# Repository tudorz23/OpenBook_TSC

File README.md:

*Designed by Marius-Tudor Zaharia, 333CA, March 2025*

# OpenBook

---

## What is OpenBook?
* OpenBook is an implementation of a performant, yet accessible e-book reader,
following an open-source philosophy, with Wi-Fi connectivity.
* It focuses on minimalism and offers a distraction-free body, with three
physical buttons for efficient navigation.
* It also promotes environmental awareness, encompassing temperature, humidity,
air pressure and air quality sensors.

---

## Block diagram

---

## Hardware description
### PCB
* The design of the PCB is centered around an **ESP32 C6 WROOM** microcontroller,
equipped with a 32-bit RISC-V single-core processor, up to 160MHz.
    * It offers 320 KB ROM, 512KB HP SRAM, 16KB LP SRAM.
    * It comes with Wi-Fi 6 and Bluetooth LE connectivity.
    * Supports GPIO, SPI, UART, I2C, LED PWM.

* The **ESP32** supports *5 power modes*, each with a different power consumption index:
    * *Active* - between 160 and 260mA
    * *Modem Sleep* - between 3 and 20mA
    * *Light Sleep* - 0.8mA
    * *Deep Sleep* - 10uA
    * *Hibernation* - 2.5uA

* **Three Buttons** are connected to 3 GPIO pins of the ESP32, allowing the user
                    to control the device:
    * *Reset* to **pin 3 - Enable**
    * *Boot* to **pin 15 - GPIO 9**
    * *Change* to **pin 23 - GPIO 15**

* **SD Card** socket, which communicates by SPI protocol:
    * *pin 2 - CD/DAT3* to **pin 4 - GPIO 4**
    * *pin 3 - CMD* to **pin 7** (MOSI, i.e. Serial Data Out, for SPI)
    * *pin 7 - DAT0* to **pin 27** (MISO, i.e. Serial Data In, for SPI)
    * *pin 5* to **pin 6 - clock**

* **E-Paper Display Header**, interfacing the external E-Ink Display, also by SPI.

* **External NOR Flash Memory 64MB**, by SPI too:
    * *pin 1 - CS* to **pin 12 - GPIO 11**
    * *pin 2* to **MOSI** (for SPI)
    * *pin 5* to **MISO** (for SPI)
    * *pin 6* to **pin 6 - clock**

* **RTC Module** - Real Time Clock, using I2C protocol:
    * *pin 4 - Reset* to **pin 16 - GPIO 18**
    * *pin 16 - SCL* to **pin 20 - GPIO 22** (for I2C)
    * *pin 15 - SDA* to **pin 19 - GPIO 21** (for I2C)
    * *pin 1* to **pin 9 - GPIO 1** (for 32KHz)
    * *pin 3 - SQW/INT* to **pin 8 - GPIO 0**
    * Has a battery backup input for continuous timekeeping.

* **BME688** - Digital low power pressure, temperature, humidity and gas sensor,
               also interfaced through I2C:
    * *pin 4 - SCK* to **pin 20 - GPIO 22** (SCL for I2C)
    * *pin 15 - SDI* to **pin 19 - GPIO 21** (SDA for I2C)
    * *pins 2, 6, 8* to **pin 17 - GPIO 19** (for I2C PW)
    * Power consumption is 3.7uA at 1Hz humidity, pressure and temperature scan
        and 0.15uA in sleep mode.

* **USB-C connector** - for fast, efficient charging.

* **Li-Po Battery Charging Controller** - MCP73831

* **LDO Voltage Regulator**

* **Battery Charge Level** - *MAX17048G+T10*, communicates by I2C interface:
    * *pin 7 - SCL* to **pin 20 - GPIO 22**
    * *pin 8 - SDA* to **pin 19 - GPIO 21**
    * Power consumption is 23uA in Active state and 3uA in Hibernate.

### External
* **7.5" E-Paper Display**
* **2500mAh Battery - LP584174**

---

## Bill Of Materials
| Component | Price (EUR) | Count | Provider | Datasheet |
| :---      | :---        | :---  | :---     | :---      |
| ESP32 C6| 2.99 | 1 | https://eu.mouser.com/ProductDetail/Espressif-Systems/ESP32-C6-WROOM-1U-N8?qs=1Kr7Jg1SGW%2FzPU4G%252ByMwkA%3D%3D | https://eu.mouser.com/datasheet/2/891/Espressif_Systems_7_11_2023_esp32_c6_wroom_1_wroom-3236277.pdf |
| USB-C connector| 0.39 | 1 | https://eu.mouser.com/ProductDetail/Same-Sky/UJC-H-G-SMT-2-P6-TR?qs=IKkN%2F947nfApFV8T6rOqww%3D%3D |https://eu.mouser.com/datasheet/2/1628/ujc_h_g_smt_2_p6_tr-3511211.pdf |
| USBLC6-2SC6Y | 0.44 | 1 | https://eu.mouser.com/ProductDetail/STMicroelectronics/USBLC6-2SC6Y?qs=gNDSiZmRJS%2FOgDexvXkdow%3D%3D | https://eu.mouser.com/datasheet/2/389/usblc6_2sc6y-1852505.pdf |
| PFMF.050.1 | 0.28 | 1 | https://eu.mouser.com/ProductDetail/Schurter/PFMF.050.2?qs=1auRipcfynCums5v1iucSA%3D%3D | https://eu.mouser.com/datasheet/2/358/typ_PFMF-1275918.pdf |
| DMG2305UX-7 | 0.19 | 2 | https://eu.mouser.com/ProductDetail/Diodes-Incorporated/DMG2305UX-7?qs=L1DZKBg7t5F%2FNBHrjfxC%252Bg%3D%3D | https://www.diodes.com/assets/Datasheets/DMG2305UX.pdf |
| SD0805S020S1R0 | 0.3 | 2 | https://eu.mouser.com/ProductDetail/KYOCERA-AVX/SD0805S020S1R0?qs=jCA%252BPfw4LHbpkAoSnwrdjw%3D%3D | https://eu.mouser.com/datasheet/2/40/schottky-3165252.pdf |
| XC6220A331MR-G | 1.46 | 1 | https://eu.mouser.com/ProductDetail/Torex-Semiconductor/XC6220A331MR-G?qs=AsjdqWjXhJ8ZSWznL1J0gg%3D%3D | https://eu.mouser.com/datasheet/2/760/xc6220-3371556.pdf |
| TANT Capacitor | 0.68 | 1 | https://eu.mouser.com/ProductDetail/Vishay-Sprague/293D107X9010D2TE3?qs=8dfOI6wKXonVqFgS8%252BQ%2FMA%3D%3D | https://www.vishay.com/docs/40002/293d.pdf |
| 112A-TAAR-R03 | 1.1 | 1 | https://store.comet.srl.ro/Catalogue/Product/43497/ | https://store.comet.bg/download-file.php?id=27596 |
| 68uH inductance | 0.9 | 1 | https://eu.mouser.com/ProductDetail/Vishay-Dale/IFDC5050JZER680M?qs=iLKYxzqNS745SePZd8tBoA%3D%3D | https://www.vishay.com/docs/34635/ifdc5050jz.pdf |
| MBR0530 | 0.14 | 3 | https://eu.mouser.com/ProductDetail/Micro-Commercial-Components-MCC/MBR0530-TP?qs=KFo7JewZbUECRHkxGanrdg%3D%3D | https://eu.mouser.com/datasheet/2/258/MBR0520_MBR0580_SOD123_-2492194.pdf |
| SI1308EDL-T1-GE3 | 0.42 | 2 | https://eu.mouser.com/ProductDetail/Vishay-Semiconductors/SI1308EDL-T1-GE3?qs=bX1%252BNvsK%2FBramh9tgpOaEw%3D%3D | https://www.vishay.com/docs/63399/si1308edl.pdf |
| Capacitor 0.1uF | 0.3 | 1 | https://eu.mouser.com/ProductDetail/KYOCERA-AVX/KGF21BR71H104KT?qs=Jm2GQyTW%2FbjYyKCvVWAEOw%3D%3D | https://eu.mouser.com/datasheet/2/40/KGF-3223650.pdf |
| Capacitor 1uF | 0.13 | 10 | https://eu.mouser.com/ProductDetail/TAIYO-YUDEN/MAASL105CC7105MFCA01?qs=HFfMDpzxxd1Fn%2FInbJA7vw%3D%3D | https://eu.mouser.com/datasheet/2/396/TAIYO_YUDEN_04_27_2024_c_mlcc_A_e1-3451516.pdf |
| Capacitor 4.7uF | 0.23 | 5 | https://eu.mouser.com/ProductDetail/KYOCERA-AVX/CM05X5R475M16AH?qs=doiCPypUmgFT1xquZKhWtQ%3D%3D | https://eu.mouser.com/datasheet/2/40/Kyocera_AVX_Components_CM025_CM05_CM105_CM21_E217K-2932876.pdf |
| Capacitor 10 uF | 0.47 | 1 | https://eu.mouser.com/ProductDetail/TDK/CGA3EDX7T1A106M080AU?qs=ZcfC38r4PovL%2FBNBUzzBFw%3D%3D | https://product.tdk.com/system/files/dam/doc/product/capacitor/ceramic/mlcc/catalog/mlcc_automotive_general_en.pdf |
| Capacitor 100nF | 0.3 | 8 | https://eu.mouser.com/ProductDetail/KYOCERA-AVX/KAM21BR71H104JT?qs=Jm2GQyTW%2Fbic6Zk4McEt6w%3D%3D | https://eu.mouser.com/datasheet/2/40/AutoMLCCKAM-3216307.pdf |
| Resistor 0.47 | 0.3 | 1 | https://eu.mouser.com/ProductDetail/SEI-Stackpole/RNCL1210FT50L0?qs=17ckDYBRdelVLOJ%252BDFjlUw%3D%3D | https://eu.mouser.com/datasheet/2/385/sei_rncl-3223524.pdf |
| Resistor 2.2 | 0.13 | 1 | https://eu.mouser.com/ProductDetail/YAGEO/RT1206FRE072R2L?qs=XhSZopxZ3H6S0nYZD83pAA%3D%3D | https://eu.mouser.com/datasheet/2/447/PYu_RT_1_to_0_01_RoHS_L_15-3461507.pdf |
| Resistor 15 | 0.25 | 1 | https://eu.mouser.com/ProductDetail/Panasonic/ERA-6AHD150V?qs=MNPzkKEzRtQip8ZeekU%252BRw%3D%3D | https://industrial.panasonic.com/cdbs/www-data/pdf/RDM0000/AOA0000C307.pdf |
Resistor 200 | 0.33 | 1 | https://eu.mouser.com/ProductDetail/TE-Connectivity-Holsworthy/RP73C2B200RFTDF?qs=n4i9pByFsMR0dWGpf721CA%3D%3D | https://eu.mouser.com/datasheet/2/418/10/ENG_DS_1773272_M1-1588495.pdf |
| Resistor 2k | 0.16 | 1 | https://eu.mouser.com/ProductDetail/Panasonic/ERA-3AED202V?qs=yocZuyCaXdM2cBmjcGkIyA%3D%3D | https://industrial.panasonic.com/cdbs/www-data/pdf/RDM0000/AOA0000C307.pdf |
| Resistor 5k1 | 0.15 | 2 | https://eu.mouser.com/ProductDetail/Vishay-Beyschlag/MCS04020C5101FE000?qs=wTZ%2FFzl837YsKPLPRIXUbg%3D%3D | https://www.vishay.com/docs/28705/mcx0x0xpro.pdf |
| Resistor 10k | 0.32 | 16 | https://eu.mouser.com/ProductDetail/SEI-Stackpole/RNWA0612BTE10K0?qs=IKkN%2F947nfD62pDKWE9ZTQ%3D%3D | https://eu.mouser.com/datasheet/2/385/SEI_RNWA-3473840.pdf |
| Resistor 100K | 0.1 | 1 | https://eu.mouser.com/ProductDetail/Panasonic/ERA-3AED104V?qs=MNPzkKEzRtQIWcmUWL4kjg%3D%3D | https://industrial.panasonic.com/cdbs/www-data/pdf/RDM0000/AOA0000C307.pdf |
| MCP73831 | 0.75 | 1 | https://eu.mouser.com/ProductDetail/Microchip-Technology/MCP73831-2ACI-MC?qs=hH%252BOa0VZEiBneYTVdpuVdg%3D%3D | https://eu.mouser.com/datasheet/2/268/MCP73831_Family_Data_Sheet_DS20001984H-3441711.pdf |
| FH34SRJ-24S-0.5SH(99) | 2.6 | 1 | https://eu.mouser.com/ProductDetail/Hirose-Connector/FH34SRJ-24S-0.5SH99?qs=vcbW%252B4%252BSTIpKBl5ap9J8Fw%3D%3D | https://eu.mouser.com/datasheet/2/185/FH34SRJ_24S_0_5SH_99__CL0580_1255_6_99_2DDrawing_0-1615044.pdf |
| BME688 | 9.86 | 1 | https://eu.mouser.com/ProductDetail/Bosch-Sensortec/BME688?qs=IS%252B4QmGtzzqQoVDscqwx3A%3D%3D | https://eu.mouser.com/datasheet/2/783/bst_bme688_fl000-2307034.pdf |
| BD5229G-TR | 0.75 | 1 | https://eu.mouser.com/ProductDetail/ROHM-Semiconductor/BD5229G-TR?qs=4kLU8WoGk0vvnhrrYwdszw%3D%3D | https://fscdn.rohm.com/en/products/databook/datasheet/ic/power/voltage_detector/bd52xxg-e.pdf |
| MAX17048G+T10 | 4.28 | 1 | https://eu.mouser.com/ProductDetail/Analog-Devices-Maxim-Integrated/MAX17048G%2bT10?qs=D7PJwyCwLAoGnnn8jEPRBQ%3D%3D | https://eu.mouser.com/datasheet/2/609/MAX17048_MAX17049-3469099.pdf |
| DS3231SN# | 14.91 | 1 | https://eu.mouser.com/ProductDetail/Analog-Devices-Maxim-Integrated/DS3231SN?qs=1eQvB6Dk1vhUlr8%2FOrV0Fw%3D%3D | https://eu.mouser.com/datasheet/2/609/DS3231-3421123.pdf |
| CPH3225A | 2.33 | 1 | https://eu.mouser.com/ProductDetail/Seiko-Semiconductors/CPH3225A?qs=3etwrb1wR%252BhUOph6lAO7eg%3D%3D | https://eu.mouser.com/datasheet/2/360/Seiko_Instruments_MicroBattery_E_20230330_2024Jan_-3561061.pdf |
| Qwiic | 3.75 | 1 | https://eu.mouser.com/ProductDetail/Adafruit/4208?qs=PzGy0jfpSMtbScLbr0L5dw%3D%3D | https://learn.adafruit.com/introducing-adafruit-stemma-qt/technical-specs |
| PGB1010603MR | 0.4 | 6 | https://eu.mouser.com/ProductDetail/Littelfuse/PGB1010603MR?qs=gu7KAQ731URLg4GSnNNN7Q%3D%3D | https://www.littelfuse.com/assetdocs/pulseguard-esd-suppressors-pgb1-datasheet?assetguid=8a337998-d54d-466b-be4e-dc5bcd1f9321 |
| W25Q512JVEIQ | 5.84 | 1 | https://eu.mouser.com/ProductDetail/Winbond/W25Q512JVEIQ?qs=l7cgNqFNU1jw6svr3at6tA%3D%3D | https://eu.mouser.com/datasheet/2/949/Winbond_W25Q512JV_Datasheet-3240039.pdf |
| LP584174 Battery| 6.4 | 1 | https://www.tme.eu/en/details/accu-lp584174_cl/rechargeable-batteries/cellevia-batteries/l584174/ | https://www.tme.eu/Document/e0683d8c34e6d878124489f71bffb6ee/cel0014.pdf |
| E-Paper Display | 48 | 1 | https://eu.mouser.com/ProductDetail/Microtips-Technology/MT-DEPG0750BNU590F1?qs=DPoM0jnrROVRMMTX0WzK%252Bw%3D%3D | https://eu.mouser.com/datasheet/2/271/MT_DEPG0750BNU590F1_V2_7-1894282.pdf |

* **Total Cost** : 124.66 EUR

---

## Implementation steps
* Firstly, I drew the schematic, with all the components.
* I drew the shape of the PCB, then I placed the components, all of them on the
top plane, taking into account the position they will occupy in the external case.
* I drew the ground plane for both top and bottom, then I used the autorouter to
shape the routes. I manually routed those that were left as airwires and corrected
the ones that were not so greatly done.
* I set the power routes to a width of 0.3mm and solved all the issues from the
DRC check, such as the angles of the routes.
* After fine-tuning the silkscreen, I pushed the PCB to 3D and placed it into
the case, alongside the battery and the display.

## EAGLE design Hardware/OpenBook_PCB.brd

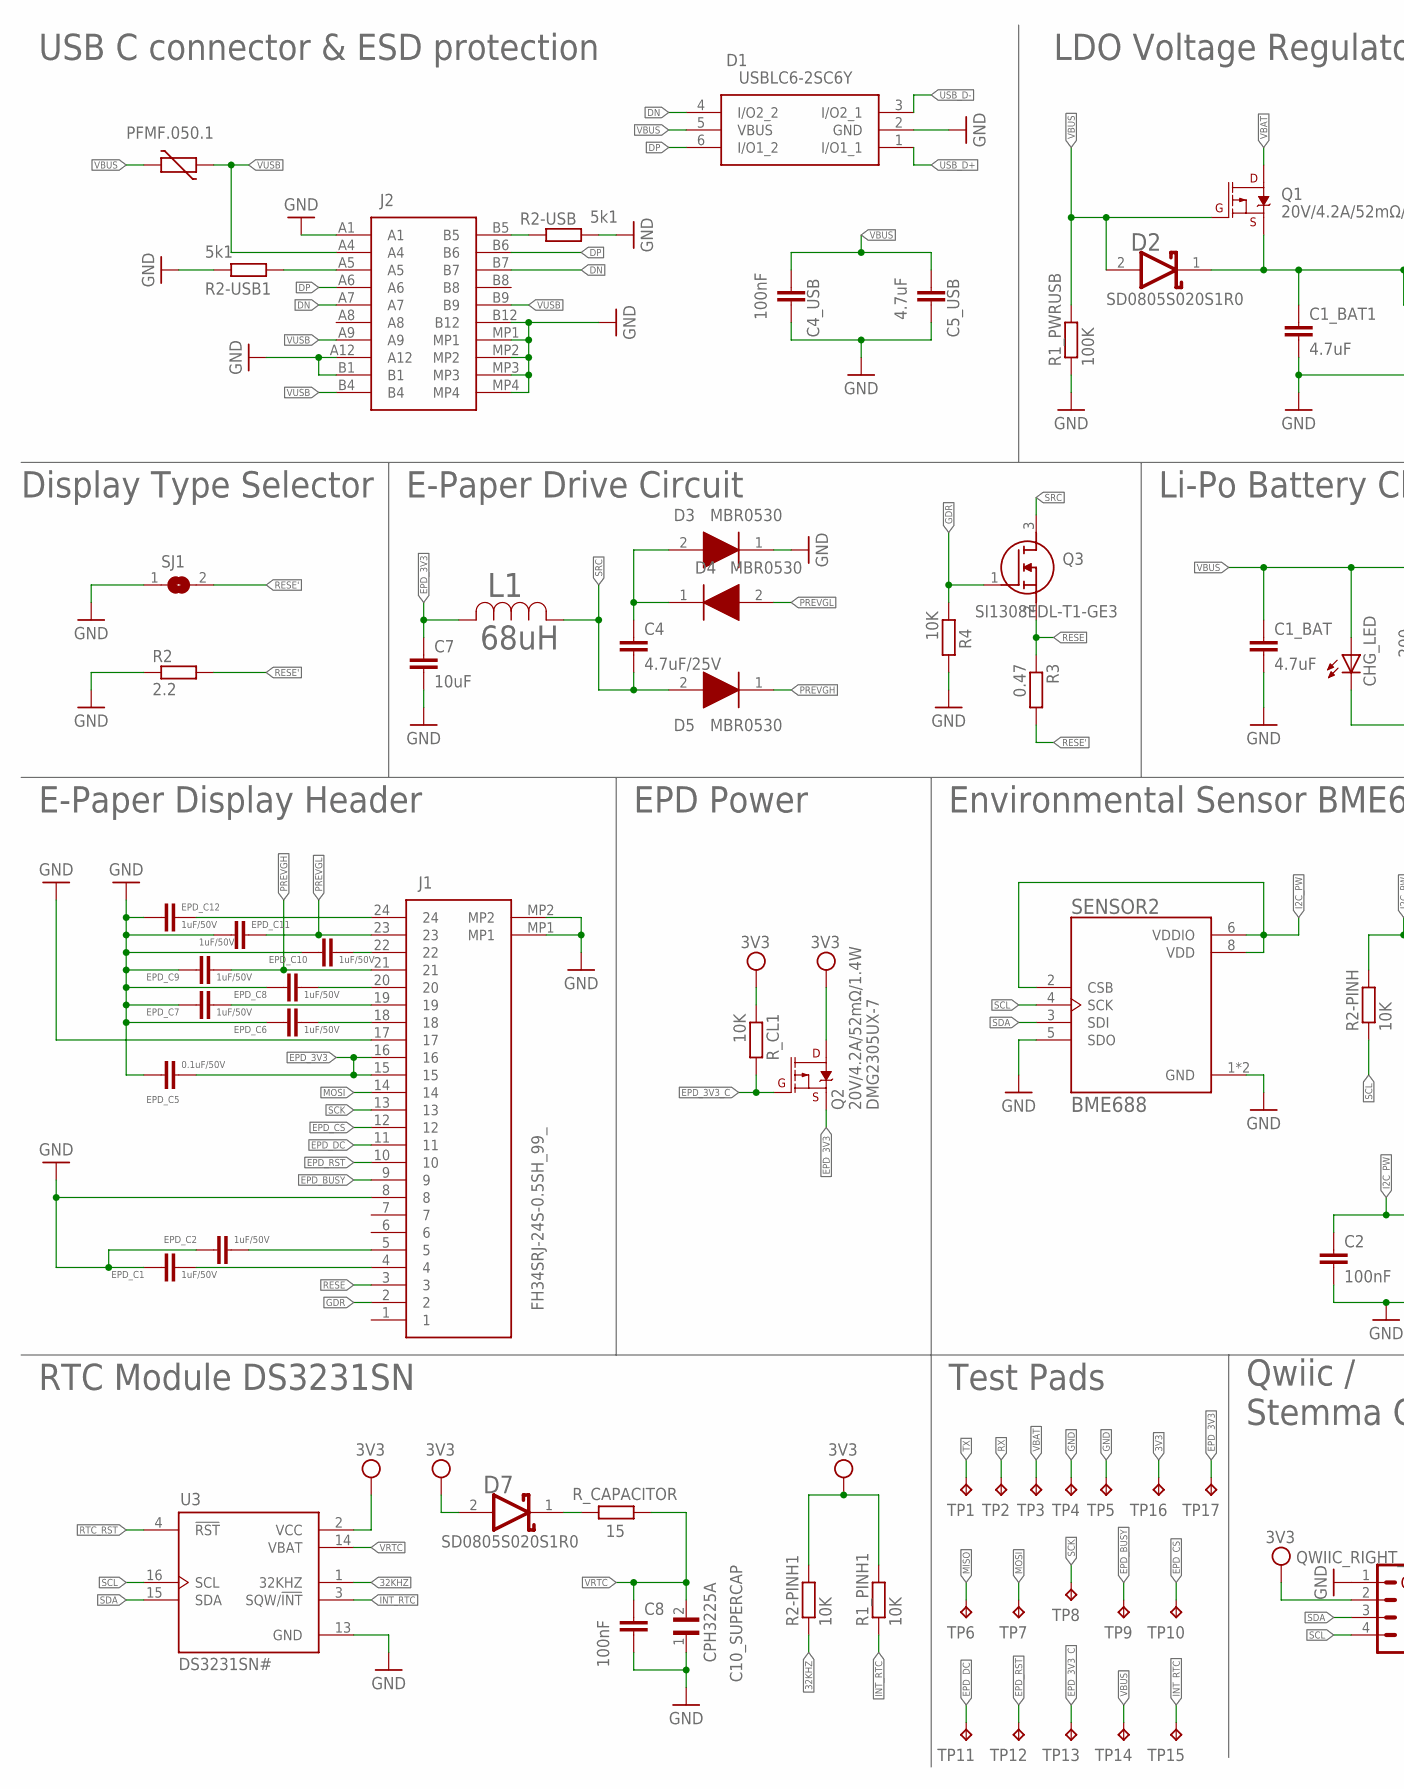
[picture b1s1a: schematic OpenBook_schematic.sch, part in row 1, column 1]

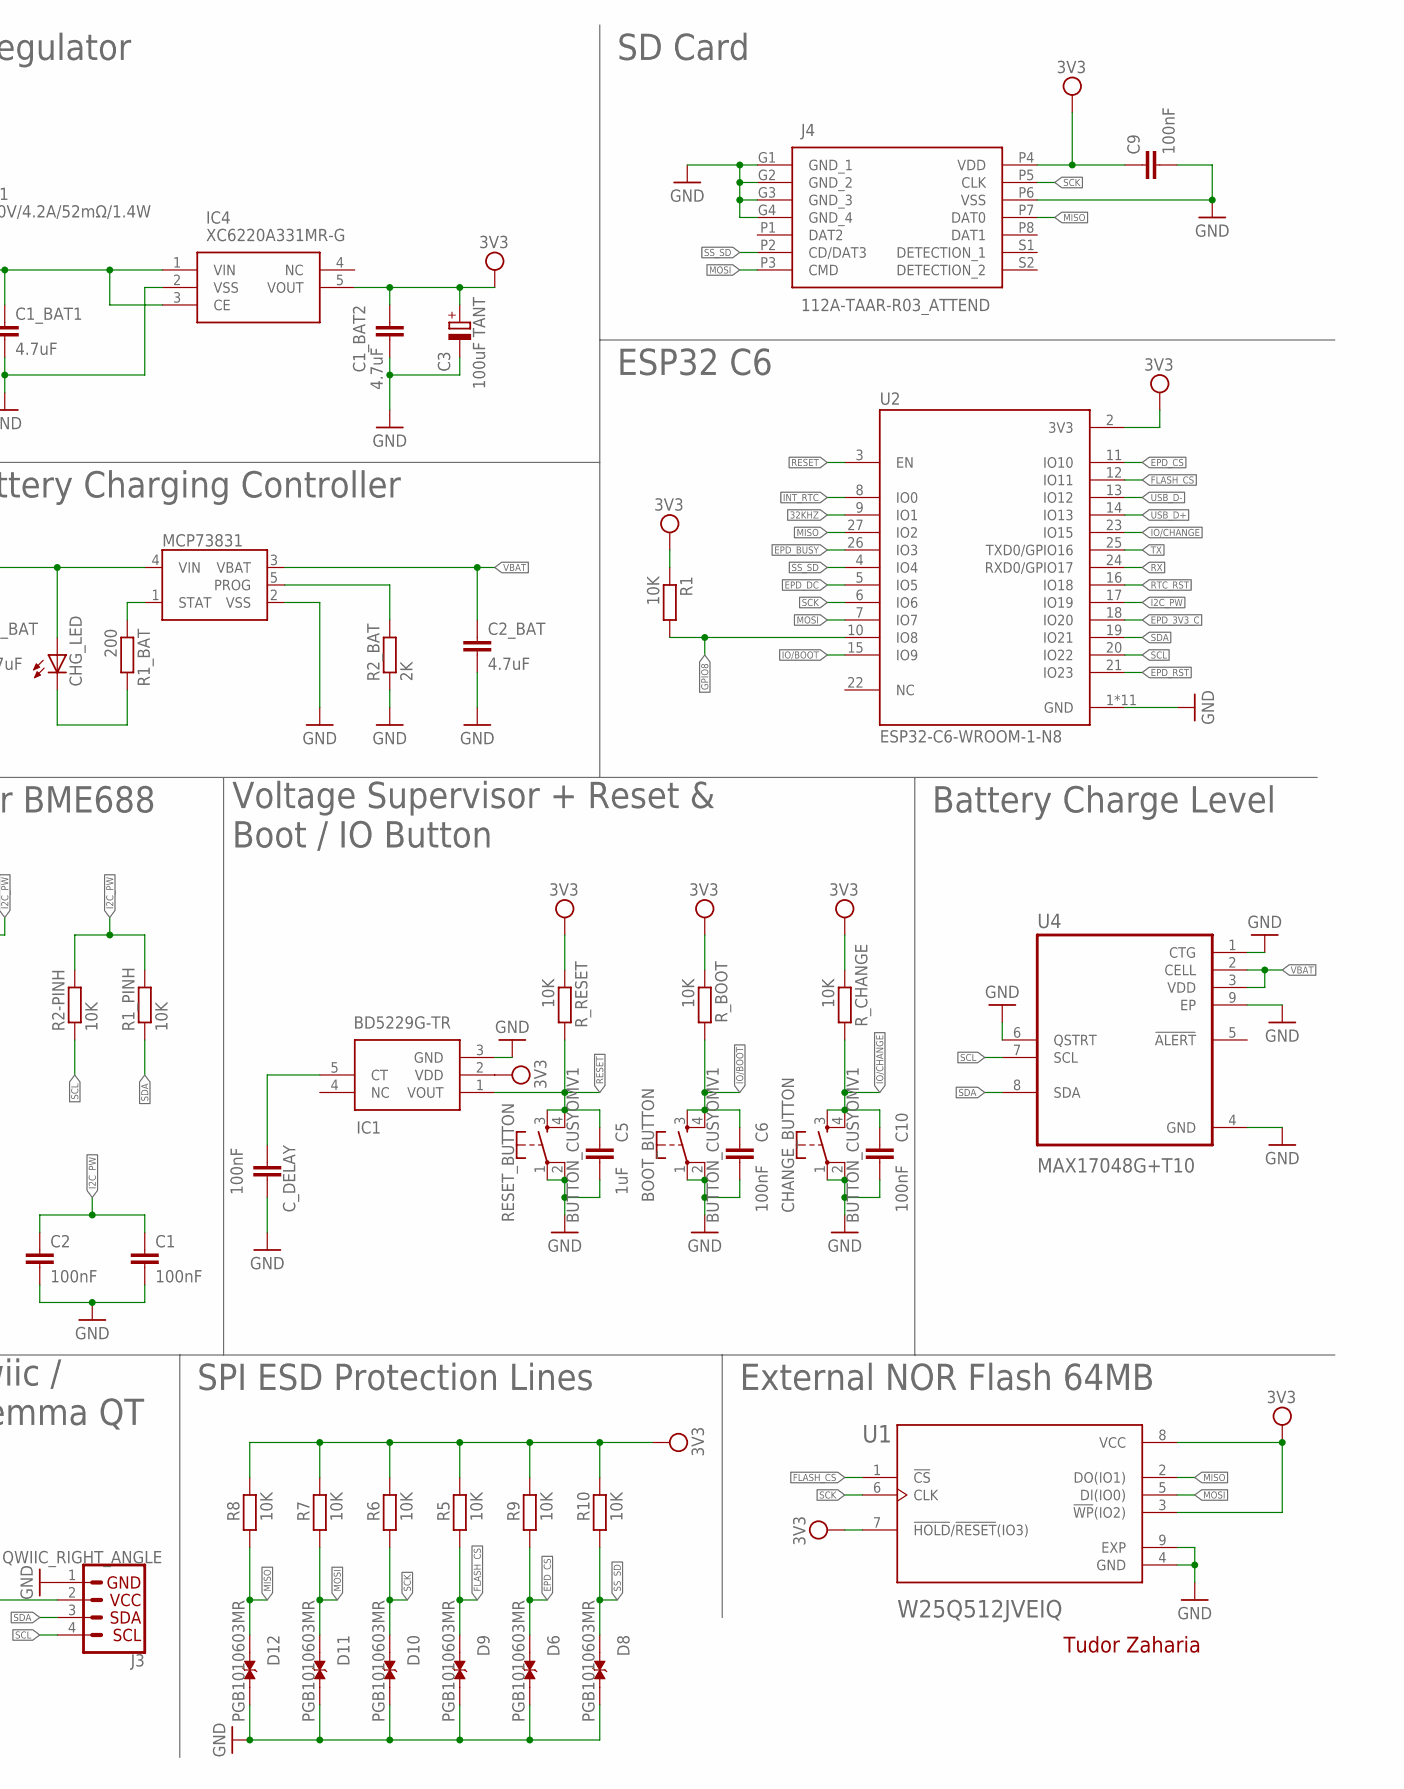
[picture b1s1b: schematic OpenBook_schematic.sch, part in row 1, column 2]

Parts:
BOOT_BUTTON: BUTTON_CUSYOMV1; MYBUTTON
C1, C2, C4_USB, C6, C8, C9, C10: 100nF; EAGLE-LTSPICE_C0402
C1_BAT, C1_BAT1, C1_BAT2, C2_BAT, C5_USB: 4.7uF; EAGLE-LTSPICE_C0402
C3: 100uF TANT; RCL_CT3528
C4: 4.7uF/25V; EAGLE-LTSPICE_C0402
C5: 1uF; EAGLE-LTSPICE_C0402
C7: 10uF; EAGLE-LTSPICE_C0402
C10_SUPERCAP: CPH3225A; CAPCP3225X100N
CHANGE_BUTTON: BUTTON_CUSYOMV1; MYBUTTON
CHG_LED: ADAFRUIT_LEDCHIP-LED0603; ADAFRUIT_CHIP-LED0603
C_DELAY: 100nF; EAGLE-LTSPICE_C0402
D1: USBLC6-2SC6Y; SOT95P280X145-6N
D2, D7: ESP32_WROVER_AVX---SD0805S020S1R0_AVX_SD0805S020S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; ESP32_WROVER_AVX---SD0805S020S1R0_AVX_SD0805S020S1R0_0
D3, D4, D5: MBR0530; SOD3716X135N
D6, D8, D9, D10, D11, D12: PGB1010603MR; DIOC1608X36N
EPD_C1, EPD_C2, EPD_C6, EPD_C7, EPD_C8, EPD_C9, EPD_C10, EPD_C11, EPD_C12: 1uF/50V; EAGLE-LTSPICE_C0402
EPD_C5: 0.1uF/50V; EAGLE-LTSPICE_C0402
IC1: BD5229G-TR; SOT95P280X125-5N
IC4: XC6220A331MR-G; SOT95P280X120-5N
J1: FH34SRJ-24S-0.5SH_99_; FH34SRJ24S05SH99
J2: SAMACSYS_PARTS_USB4110-GF-A; SAMACSYS_PARTS_USB4110GFA
J3: QWIIC_RIGHT_ANGLE; JST04_1MM_RA
J4: 112A-TAAR-R03_ATTEND; 112ATAARR03ATTEND
L1: 68uH; IND_4828-WE-TPC_WRE
MCP73831: ESP32_WROVER_SPARKFUN-IC-POWER_MCP73831; ESP32_WROVER_SPARKFUN-IC-POWER_SOT23-5
PFMF.050.1: ESP32C6_VARISTORCN1812; ESP32C6_VARISTOR_CT/CN1812
Q1, Q2: 20V/4.2A/52mΩ/1.4W; ESP32_WROVER_SPARKFUN-DISCRETESEMI_SOT23-3
Q3: SI1308EDL-T1-GE3; SOT65P210X110-3N
R1, R1_PINH, R1_PINH1, R2-PINH, R2-PINH1, R4, R5, R6, R7, R8, R9, R10: 10K; ESP32_WROVER_EAGLE-LTSPICE_R0402
R1_BAT: 200; ESP32_WROVER_EAGLE-LTSPICE_R0402
R1_PWRUSB: 100K; ESP32_WROVER_EAGLE-LTSPICE_R0402
R2: 2.2; ESP32_WROVER_EAGLE-LTSPICE_R0402
R2-USB, R2-USB1: 5k1; ESP32_WROVER_EAGLE-LTSPICE_R0402
R2_BAT: 2K; ESP32_WROVER_EAGLE-LTSPICE_R0402
R3: 0.47; ESP32_WROVER_EAGLE-LTSPICE_R0402
RESET_BUTTON: BUTTON_CUSYOMV1; MYBUTTON
R_BOOT: 10K; ESP32_WROVER_EAGLE-LTSPICE_R0402
R_CAPACITOR: 15; ESP32_WROVER_EAGLE-LTSPICE_R0402
R_CHANGE: 10K; ESP32_WROVER_EAGLE-LTSPICE_R0402
R_CL1: 10K; ESP32_WROVER_EAGLE-LTSPICE_R0402
R_RESET: 10K; ESP32_WROVER_EAGLE-LTSPICE_R0402
SENSOR2: BME688; ESP32_WROVER_BME680_PSON80P300X300X100-8N
SJ1: SJ
TP1: TX; TP20R
TP2: RX; TP20R
TP3: VBAT; TP20R
TP4, TP5: GND; TP20R
TP6: MISO; TP20R
TP7: MOSI; TP20R
TP8: SCK; TP20R
TP9: EPD_BUSY; TP20R
TP10: EPD_CS; TP20R
TP11: EPD_DC; TP20R
TP12: EPD_RST; TP20R
TP13: EPD_3V3_C; TP20R
TP14: VBUS; TP20R
TP15: INT_RTC; TP20R
TP16: 3V3; TP20R
TP17: EPD_3V3; TP20R
U1: W25Q512JVEIQ; SON127P600X800X80-9N
U2: ESP32-C6-WROOM-1-N8; XCVR_ESP32-C6-WROOM-1-N8
U3: DS3231SN#; SOIC127P1032X265-16N
U4: MAX17048G+T10; SON50P200X200X80-9N

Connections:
3V3: C1_BAT2.1, C3.+, C9.1, D7.2 (ANODE), IC1.2 (VDD), IC4.5 (VOUT), J3.2, J4.P4 (VDD), Q2.3 (D), R1.1, R1_PINH1.2, R2-PINH1.2, R5.2, R6.2, R7.2, R8.2, R9.2, R10.2, R_BOOT.1, R_CHANGE.1, R_CL1.1, R_RESET.1, TP16.TP, U1.3 (!WP!(IO2)), U1.7 (!HOLD!/!RESET!(IO3)), U1.8 (VCC), U2.2 (3V3), U3.2 (VCC)
32KHZ: R2-PINH1.1, U2.9 (IO1), U3.1 (32KHZ)
DN: D1.4 (I/O2_2), J2.A7, J2.B7
DP: D1.6 (I/O1_2), J2.A6, J2.B6
EPD_3V3: C7.1, EPD_C5.1, J1.15, J1.16, L1.2, Q2.2 (S), TP17.TP
EPD_3V3_C: Q2.1 (G), R_CL1.2, TP13.TP, U2.18 (IO20)
EPD_BUSY: J1.9, TP9.TP, U2.26 (IO3)
EPD_CS: D6.1, J1.12, R9.1, TP10.TP, U2.11 (IO10)
EPD_DC: J1.11, TP11.TP, U2.5 (IO5)
EPD_RST: J1.10, TP12.TP, U2.21 (IO23)
FLASH_CS: D9.1, R5.1, U1.1 (!CS), U2.12 (IO11)
GDR: J1.2, Q3.1 (G), R4.1
GND: BOOT_BUTTON.1, BOOT_BUTTON.2, C1.2, C1_BAT.2, C1_BAT1.2, C1_BAT2.2, C2.2, C2_BAT.2, C3.-, C4_USB.2, C5.2, C5_USB.2, C6.2, C7.2, C8.2, C9.2, C10.2, C10_SUPERCAP.1, CHANGE_BUTTON.1, CHANGE_BUTTON.2, C_DELAY.2, D1.2 (GND), D3.1 (K), D6.2, D8.2, D9.2, D10.2, D11.2, D12.2, EPD_C1.2, EPD_C2.2, EPD_C5.2, EPD_C6.2, EPD_C7.2, EPD_C8.2, EPD_C9.2, EPD_C10.2, EPD_C11.2, EPD_C12.2, IC1.3 (GND), IC4.2 (VSS), J1.8, J1.17, J1.MP1, J1.MP2, J2.A1, J2.A12, J2.B1, J2.B12, J2.MP1, J2.MP2, J2.MP3, J2.MP4, J3.1, J4.G1 (GND_1), J4.G2 (GND_2), J4.G3 (GND_3), J4.G4 (GND_4), J4.P6 (VSS), MCP73831.2 (VSS), R1_PWRUSB.1, R2.1, R2-USB.2, R2-USB1.1, R2_BAT.1, R4.2, RESET_BUTTON.1, RESET_BUTTON.2, SENSOR2.1 (GND), SENSOR2.5 (SDO), SENSOR2.7 (GND), SJ1.1, TP4.TP, TP5.TP, U1.4 (GND), U1.9 (EXP), U2.1 (GND), U2.28 (GND), U2.29_1 (GND), U2.29_2 (GND), U2.29_3 (GND), U2.29_4 (GND), U2.29_5 (GND), U2.29_6 (GND), U2.29_7 (GND), U2.29_8 (GND), U2.29_9 (GND), U3.13 (GND), U4.1 (CTG), U4.4 (GND), U4.6 (QSTRT), U4.9 (EP)
GPIO8: R1.2, U2.10 (IO8)
I2C_PW: C1.1, C2.1, R1_PINH.2, R2-PINH.2, SENSOR2.2 (CSB), SENSOR2.6 (VDDIO), SENSOR2.8 (VDD), U2.17 (IO19)
INT_RTC: R1_PINH1.1, TP15.TP, U2.8 (IO0), U3.3 (SQW/!INT)
IO/BOOT: BOOT_BUTTON.3, BOOT_BUTTON.4, C6.1, R_BOOT.2, U2.15 (IO9)
IO/CHANGE: C10.1, CHANGE_BUTTON.3, CHANGE_BUTTON.4, R_CHANGE.2, U2.23 (IO15)
MISO: D12.1, J4.P7 (DAT0), R8.1, TP6.TP, U1.2 (DO(IO1)), U2.27 (IO2)
MOSI: D11.1, J1.14, J4.P3 (CMD), R7.1, TP7.TP, U1.5 (DI(IO0)), U2.7 (IO7)
unnamed: J2.A5, R2-USB1.2
unnamed: J2.B5, R2-USB.1
unnamed: C1_BAT1.1, D2.1 (CATHODE), IC4.1 (VIN), IC4.3 (CE), Q1.2 (S)
unnamed: C4.1, D3.2 (A), D4.1 (K)
unnamed: MCP73831.1 (STAT), R1_BAT.1
unnamed: CHG_LED.C, R1_BAT.2
unnamed: MCP73831.5 (PROG), R2_BAT.2
unnamed: EPD_C12.1, J1.24
unnamed: D7.1 (CATHODE), R_CAPACITOR.2
unnamed: EPD_C10.1, J1.22
unnamed: C_DELAY.1, IC1.5 (CT)
unnamed: EPD_C8.1, J1.20
unnamed: EPD_C7.1, J1.19
unnamed: EPD_C6.1, J1.18
unnamed: EPD_C2.1, J1.5
unnamed: EPD_C1.1, J1.4
PREVGH: D5.1 (K), EPD_C9.1, J1.21
PREVGL: D4.2 (A), EPD_C11.1, J1.23
RESE: J1.3, Q3.2 (S), R3.1
RESE': R2.2, R3.2, SJ1.2
RESET: C5.1, IC1.1 (VOUT), RESET_BUTTON.3, RESET_BUTTON.4, R_RESET.2, U2.3 (EN)
RTC_RST: U2.16 (IO18), U3.4 (!RST)
RX: TP2.TP, U2.24 (RXD0/GPIO17)
SCK: D10.1, J1.13, J4.P5 (CLK), R6.1, TP8.TP, U1.6 (CLK), U2.6 (IO6)
SCL: J3.4, R2-PINH.1, SENSOR2.4 (SCK), U2.20 (IO22), U3.16 (SCL), U4.7 (SCL)
SDA: J3.3, R1_PINH.1, SENSOR2.3 (SDI), U2.19 (IO21), U3.15 (SDA), U4.8 (SDA)
SRC: C4.2, D5.2 (A), L1.1, Q3.3 (D)
SS_SD: D8.1, J4.P2 (CD/DAT3), R10.1, U2.4 (IO4)
TX: TP1.TP, U2.25 (TXD0/GPIO16)
USB_D+: D1.1 (I/O1_1), U2.14 (IO13)
USB_D-: D1.3 (I/O2_1), U2.13 (IO12)
VBAT: C2_BAT.1, MCP73831.3 (VBAT), Q1.3 (D), TP3.TP, U4.2 (CELL), U4.3 (VDD)
VBUS: C1_BAT.1, C4_USB.1, C5_USB.1, CHG_LED.A, D1.5 (VBUS), D2.2 (ANODE), MCP73831.4 (VIN), PFMF.050.1.2, Q1.1 (G), R1_PWRUSB.2, TP14.TP
VRTC: C8.1, C10_SUPERCAP.2, R_CAPACITOR.1, U3.14 (VBAT)
VUSB: J2.A4, J2.A9, J2.B4, J2.B9, PFMF.050.1.1

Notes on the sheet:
USB C connector & ESD protection
LDO Voltage Regulator
SD Card
Display Type Selector
E-Paper Drive Circuit
Li-Po Battery Charging Controller
ESP32 C6
E-Paper Display Header
EPD Power
Environmental Sensor BME688
Voltage Supervisor + Reset & Boot / IO Button
Battery Charge Level
RTC Module DS3231SN
Test Pads
Qwiic / Stemma QT
SPI ESD Protection Lines
External NOR Flash 64MB
Tudor Zaharia
DMG2305UX-7
SD0805S020S1R0

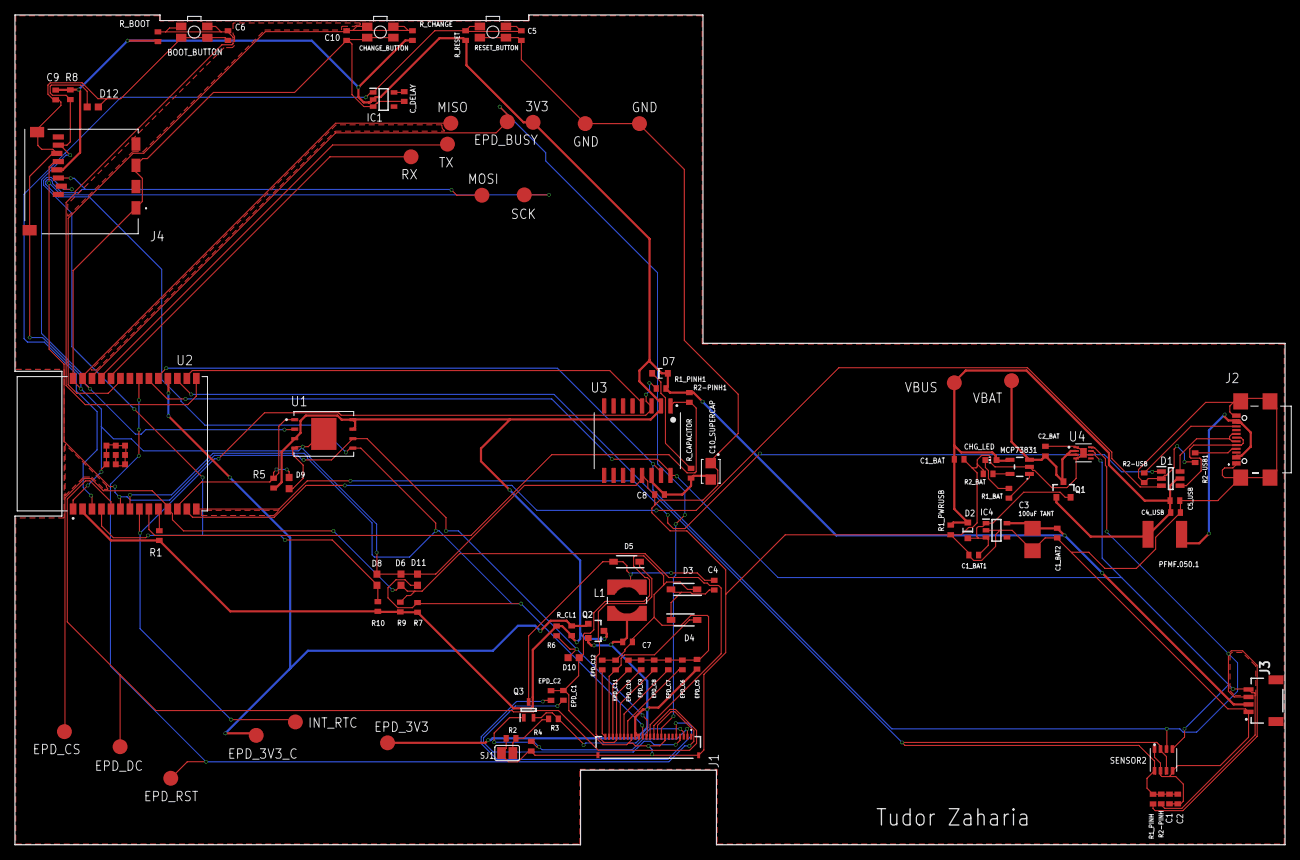
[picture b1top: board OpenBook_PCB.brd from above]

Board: 2 copper layers, 170.2 x 111.2 mm, 103 parts (0 on the bottom side), 55 nets.

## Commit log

2025-03-23 First commit.
2025-03-23 Test image adding.
2025-03-23 Finished README.
2025-03-23 Added design files.
2025-03-23 Corrected name of the file.
2025-03-24 Added images and finalised Readme.
2025-03-30 Updated design files.
2025-03-30 Updated images.
2025-04-11 Solved all issues. Final product.

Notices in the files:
parts and their libraries:
COPYRIGHT: Copyright (C) 2024 Ultra Librarian. All rights reserved.
